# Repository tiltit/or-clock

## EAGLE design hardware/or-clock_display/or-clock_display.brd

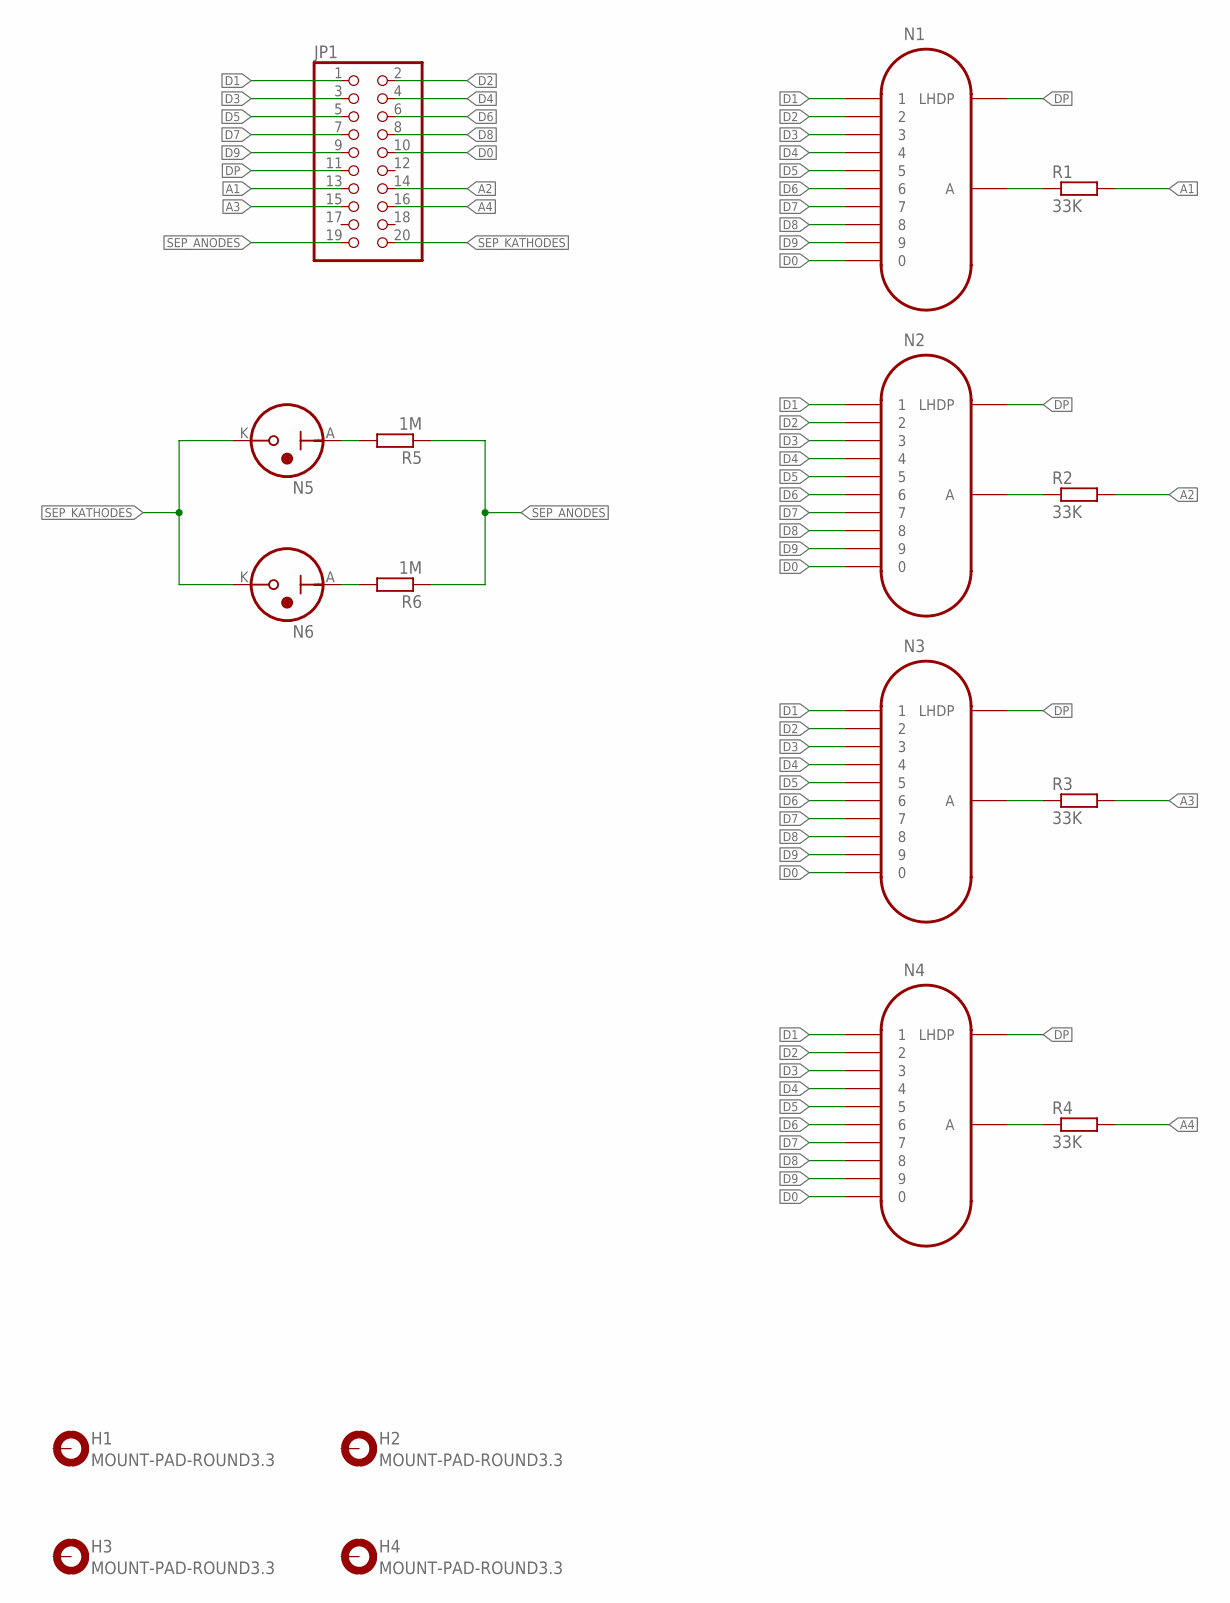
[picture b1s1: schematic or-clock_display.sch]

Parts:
H1, H2, H3, H4: MOUNT-PAD-ROUND3.3; 3,3-PAD
JP1: PINHD-2X10; 2X10
N1, N2, N3, N4: IN-12B; IN-12
N5, N6: INS-1
R1, R2, R3, R4: 33K; 0207/7
R5, R6: 1M; 0207/7

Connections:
A1: JP1.13, R1.2
A2: JP1.14, R2.2
A3: JP1.15, R3.2
A4: JP1.16, R4.2
D0: JP1.10, N1.0, N2.0, N3.0, N4.0
D1: JP1.1, N1.1, N2.1, N3.1, N4.1
D2: JP1.2, N1.2, N2.2, N3.2, N4.2
D3: JP1.3, N1.3, N2.3, N3.3, N4.3
D4: JP1.4, N1.4, N2.4, N3.4, N4.4
D5: JP1.5, N1.5, N2.5, N3.5, N4.5
D6: JP1.6, N1.6, N2.6, N3.6, N4.6
D7: JP1.7, N1.7, N2.7, N3.7, N4.7
D8: JP1.8, N1.8, N2.8, N3.8, N4.8
D9: JP1.9, N1.9, N2.9, N3.9, N4.9
DP: JP1.11, N1.LHDP, N2.LHDP, N3.LHDP, N4.LHDP
unnamed: N1.A, R1.1
unnamed: N2.A, R2.1
unnamed: N3.A, R3.1
unnamed: N4.A, R4.1
unnamed: N5.A, R5.2
unnamed: N6.A, R6.2
SEP_ANODES: JP1.19, R5.1, R6.1
SEP_KATHODES: JP1.20, N5.K, N6.K

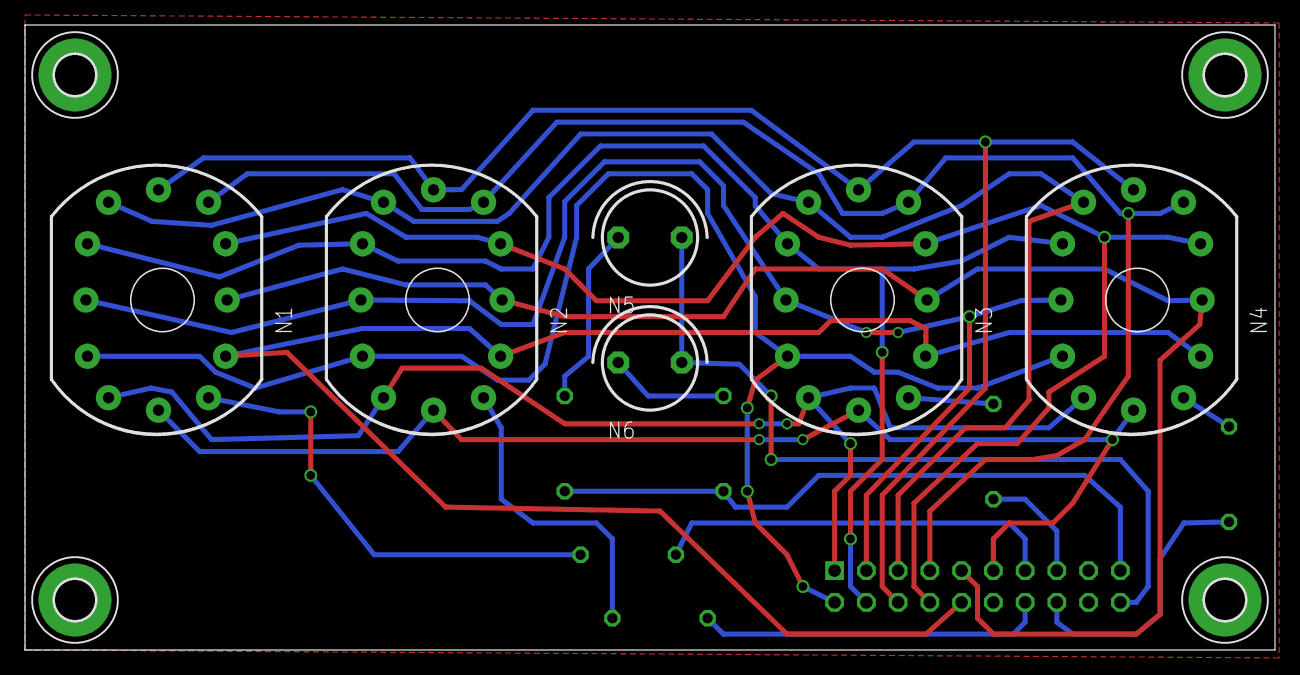
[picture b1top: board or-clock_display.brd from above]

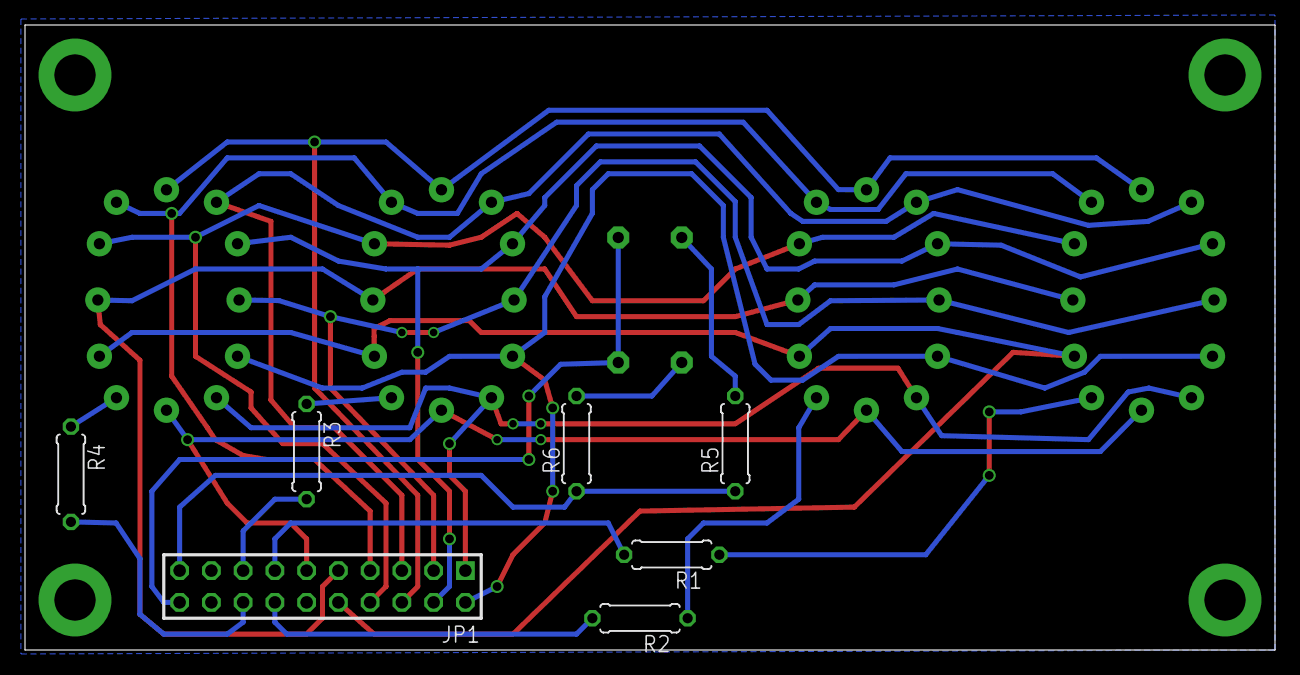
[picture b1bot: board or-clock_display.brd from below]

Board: 2 copper layers, 100.0 x 50.0 mm, 17 parts (7 on the bottom side), 23 nets.

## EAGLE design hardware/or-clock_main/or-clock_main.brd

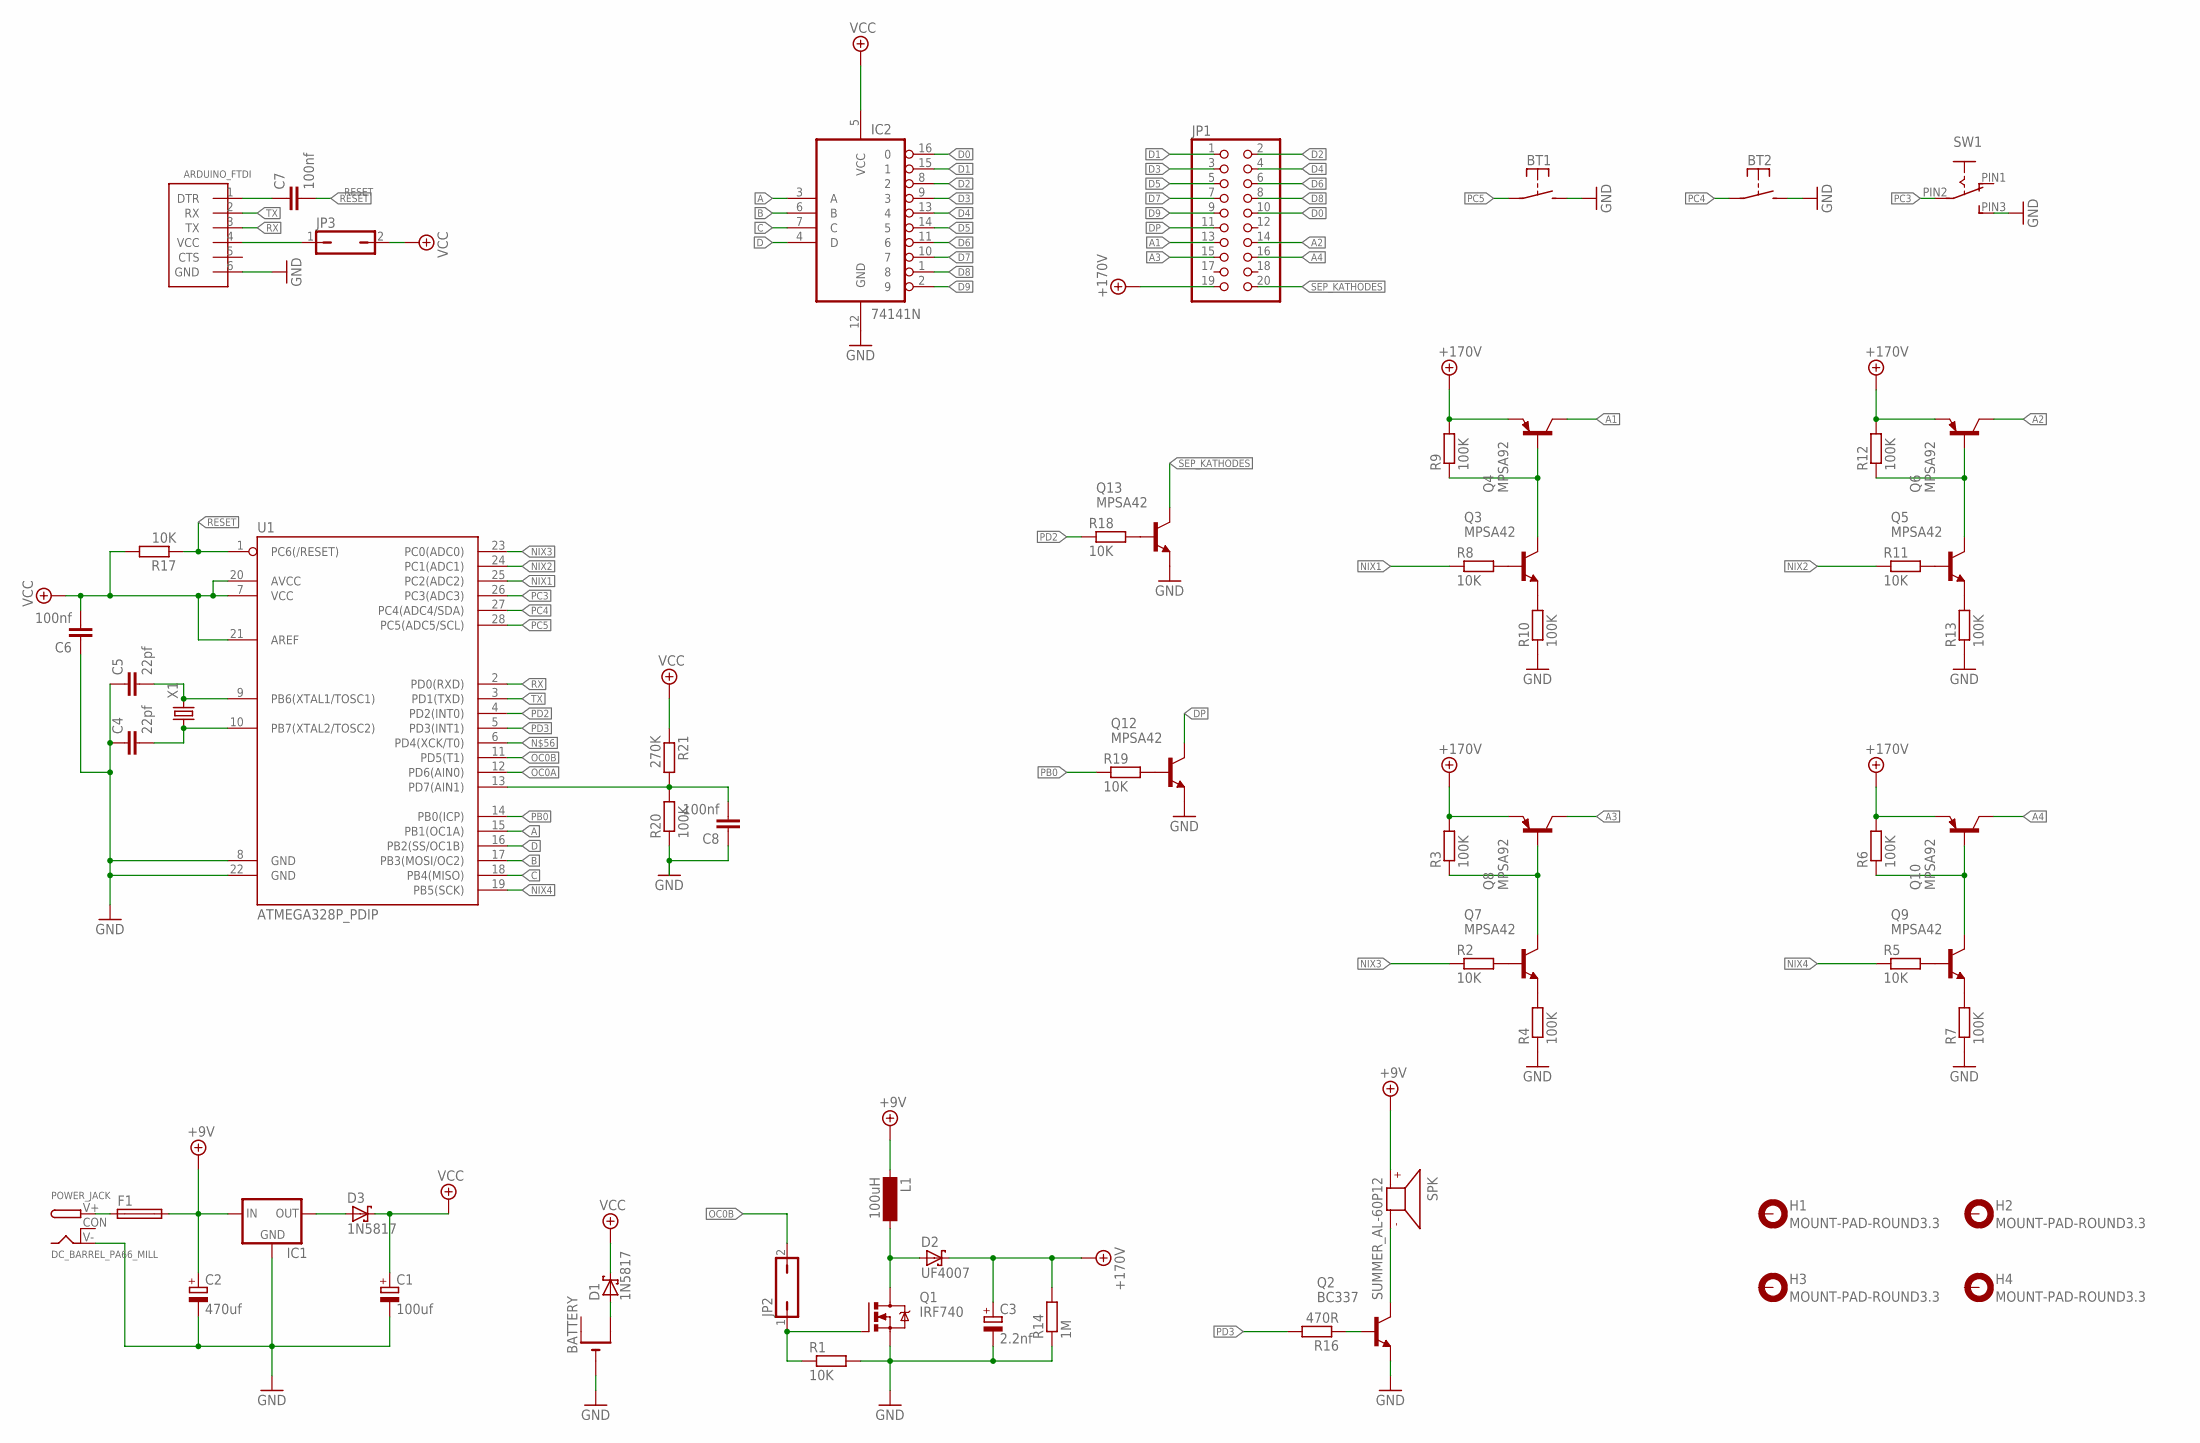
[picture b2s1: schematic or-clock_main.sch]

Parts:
BATTERY: CR1220THM; CR1220-THM
BT1, BT2: SWITCH_3305D; BUT3305D
C1: 100uf; E5-6
C2: 470uf; E5-10,5
C3: 2.2nf; E5-8,5
C4, C5: 22pf; C025-025X050
C6, C7, C8: 100nf; C025-025X050
D1, D3: 1N5817; DO41-7.6
D2: UF4007; DO41-7.6
F1: LITTLEFUSE
H1, H2, H3, H4: MOUNT-PAD-ROUND3.3; 3,3-PAD
IC1: 78XXS
IC2: 74141N; DIL16
JP1: PINHD-2X10_FEMALE; 2X10
JP2, JP3: JP1Q; JP1
L1: 100uH; BS11
POWER_JACK: DC_BARREL_PA66_MILL; PA66_DC_JACK_MILL
Q1: IRF740; TO220BV
Q2: BC337; TO92-
Q3, Q5, Q7, Q9, Q12, Q13: MPSA42; TO92-
Q4, Q6, Q8, Q10: MPSA92; TO92-
R1, R2, R5, R8, R11, R17, R18, R19: 10K; 0207/2V
R3, R4, R6, R7, R9, R10, R12, R13, R20: 100K; 0207/2V
R14: 1M; 0207/7
R16: 470R; 0207/2V
R21: 270K; 0207/2V
SERIAL_CON: ARDUINO_FTDI_HEADERV; 1X06
SPK: SUMMER_AL-60P12; AL-60P12_SUMMER
SW1: 13P_SW; TS-13P
U1: ATMEGA328P_PDIP; DIL28-3
X1: CRYSTALTC26V; TC26V

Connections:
+5V: C1.+, C6.2, D1.C, D3.C, IC2.5 (VCC), JP3.2, R17.2, R21.1, U1.7 (VCC), U1.20 (AVCC), U1.21 (AREF)
+9V: C2.+, F1.2, IC1.IN, L1.1, SPK.POS (+)
+170V: C3.+, D2.C, JP1.19, Q4.3 (E), Q6.3 (E), Q8.3 (E), Q10.3 (E), R3.2, R6.2, R9.2, R12.2, R14.2
A: IC2.3 (A), U1.15 (PB1(OC1A))
A1: JP1.13, Q4.1 (C)
A2: JP1.14, Q6.1 (C)
A3: JP1.15, Q8.1 (C)
A4: JP1.16, Q10.1 (C)
B: IC2.6 (B), U1.17 (PB3(MOSI/OC2))
C: IC2.7 (C), U1.18 (PB4(MISO))
D: IC2.4 (D), U1.16 (PB2(SS/OC1B))
D0: IC2.16 (0), JP1.10
D1: IC2.15 (1), JP1.1
D2: IC2.8 (2), JP1.2
D3: IC2.9 (3), JP1.3
D4: IC2.13 (4), JP1.4
D5: IC2.14 (5), JP1.5
D6: IC2.11 (6), JP1.6
D7: IC2.10 (7), JP1.7
D8: IC2.1 (8), JP1.8
D9: IC2.2 (9), JP1.9
DP: JP1.11, Q12.1 (C)
GND: BATTERY.-, BT1.P$2 (S), BT2.P$2 (S), C1.-, C2.-, C3.-, C4.1, C5.1, C6.1, C8.1, IC1.GND, IC2.12 (GND), POWER_JACK.V- (GND), Q1.S, Q2.1 (E), Q12.3 (E), Q13.3 (E), R1.2, R4.1, R7.1, R10.1, R13.1, R14.1, R20.1, SERIAL_CON.6 (GND), SW1.PIN3 (S), U1.8 (GND), U1.22 (GND)
GNDBREAK: POWER_JACK.CON (GNDBREAK)
unnamed: BATTERY.+2 (+1), D1.A
unnamed: D2.A, L1.2, Q1.D
unnamed: D3.A, IC1.OUT
unnamed: Q7.2 (B), R2.2
unnamed: Q7.3 (E), R4.2
unnamed: Q7.1 (C), Q8.2 (B), R3.1
unnamed: Q9.2 (B), R5.2
unnamed: Q9.1 (C), Q10.2 (B), R6.1
unnamed: Q9.3 (E), R7.2
unnamed: Q3.2 (B), R8.2
unnamed: Q3.1 (C), Q4.2 (B), R9.1
unnamed: Q3.3 (E), R10.2
unnamed: Q5.2 (B), R11.2
unnamed: Q5.1 (C), Q6.2 (B), R12.1
unnamed: Q5.3 (E), R13.2
unnamed: F1.1, POWER_JACK.V+ (PWR)
unnamed: Q2.2 (B), R16.1
unnamed: Q2.3 (C), SPK.NEG (-)
unnamed: JP3.1, SERIAL_CON.4 (VCC)
unnamed: C7.1, SERIAL_CON.1 (DTR)
unnamed: C5.2, U1.9 (PB6(XTAL1/TOSC1)), X1.2
unnamed: C4.2, U1.10 (PB7(XTAL2/TOSC2)), X1.1
unnamed: Q13.2 (B), R18.2
unnamed: Q12.2 (B), R19.2
unnamed: C8.2, R20.2, R21.2, U1.13 (PD7(AIN1))
NIX1: R8.1, U1.25 (PC2(ADC2))
NIX2: R11.1, U1.24 (PC1(ADC1))
NIX3: R2.1, U1.23 (PC0(ADC0))
NIX4: R5.1, U1.19 (PB5(SCK))
OC0A: U1.12 (PD6(AIN0))
OC0B: JP2.2, U1.11 (PD5(T1))
PB0: R19.1, U1.14 (PB0(ICP))
PC3: SW1.PIN2, U1.26 (PC3(ADC3))
PC4: BT2.P$1, U1.27 (PC4(ADC4/SDA))
PC5: BT1.P$1, U1.28 (PC5(ADC5/SCL))
PD2: R18.1, U1.4 (PD2(INT0))
PD3: R16.2, U1.5 (PD3(INT1))
PWM: JP2.1, Q1.G, R1.1
RESET: C7.2, R17.1, U1.1 (PC6(/RESET))
RX: SERIAL_CON.3 (TX), U1.2 (PD0(RXD))
SEP_KATHODES: JP1.20, Q13.1 (C)
TX: SERIAL_CON.2 (RX), U1.3 (PD1(TXD))

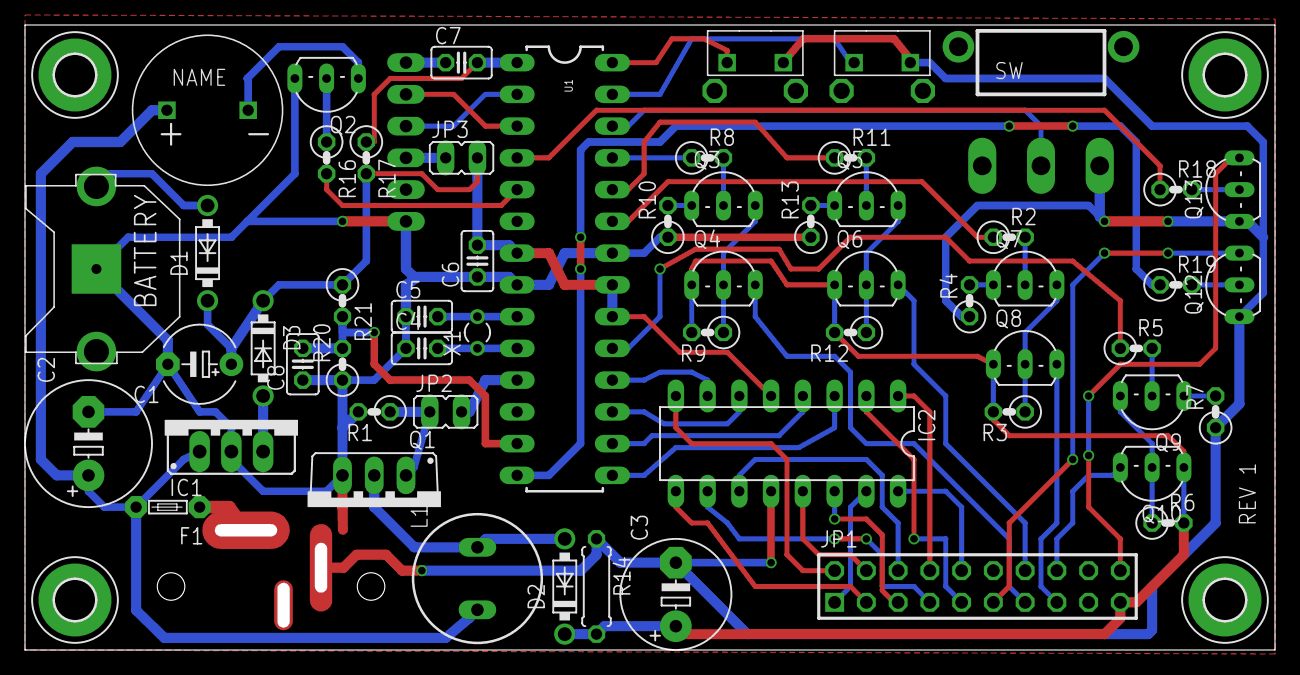
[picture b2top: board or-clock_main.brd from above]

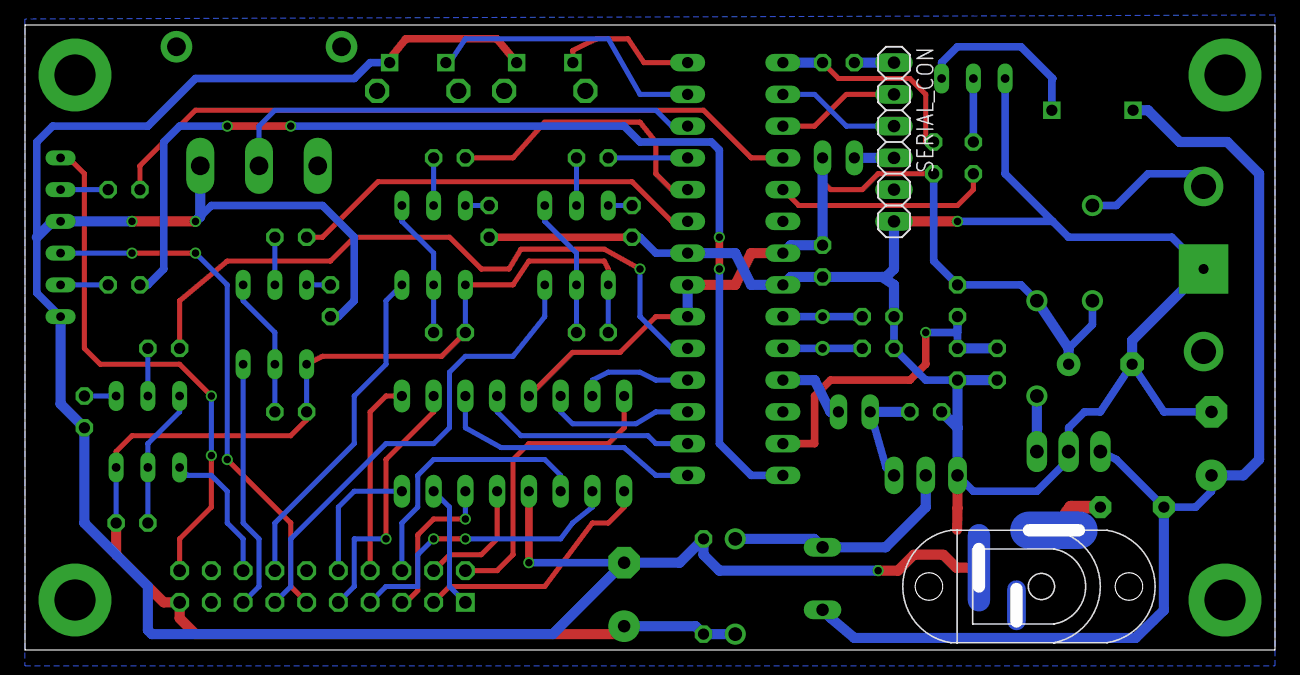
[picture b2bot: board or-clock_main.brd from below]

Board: 2 copper layers, 99.0 x 49.0 mm, 63 parts (2 on the bottom side), 64 nets.

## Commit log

2015-05-22 rock on
2015-10-25 removed old eagle files
2015-10-25 Added new Kicad files
